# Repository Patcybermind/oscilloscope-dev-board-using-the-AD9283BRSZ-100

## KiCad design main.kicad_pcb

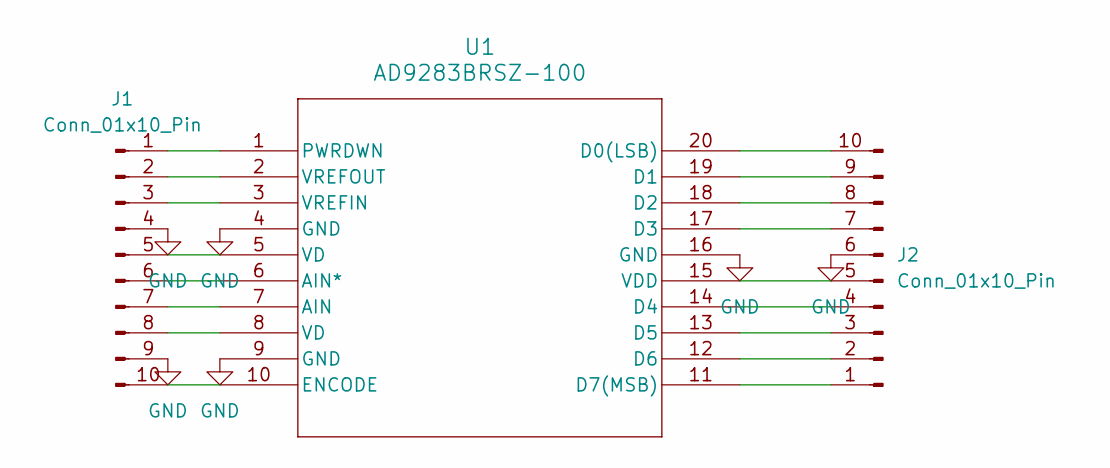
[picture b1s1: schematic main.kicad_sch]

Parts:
J1, J2: Conn_01x10_Pin; PinHeader_1x10_P2.54mm_Vertical
U1: AD9283BRSZ-100; RS_20_ADI

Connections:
GND: J1.4, J1.9, J2.6, U1.4 (GND), U1.9 (GND), U1.16 (GND)
unnamed: J1.1, U1.1 (PWRDWN)
unnamed: J1.2, U1.2 (VREFOUT)
unnamed: J1.3, U1.3 (VREFIN)
unnamed: J1.5, U1.5 (VD)
unnamed: J1.6, U1.6 (AIN*)
unnamed: J1.7, U1.7 (AIN)
unnamed: J1.8, U1.8 (VD)
unnamed: J1.10, U1.10 (ENCODE)
unnamed: J2.1, U1.11 (D7(MSB))
unnamed: J2.2, U1.12 (D6)
unnamed: J2.3, U1.13 (D5)
unnamed: J2.4, U1.14 (D4)
unnamed: J2.5, U1.15 (VDD)
unnamed: J2.7, U1.17 (D3)
unnamed: J2.8, U1.18 (D2)
unnamed: J2.9, U1.19 (D1)
unnamed: J2.10, U1.20 (D0(LSB))

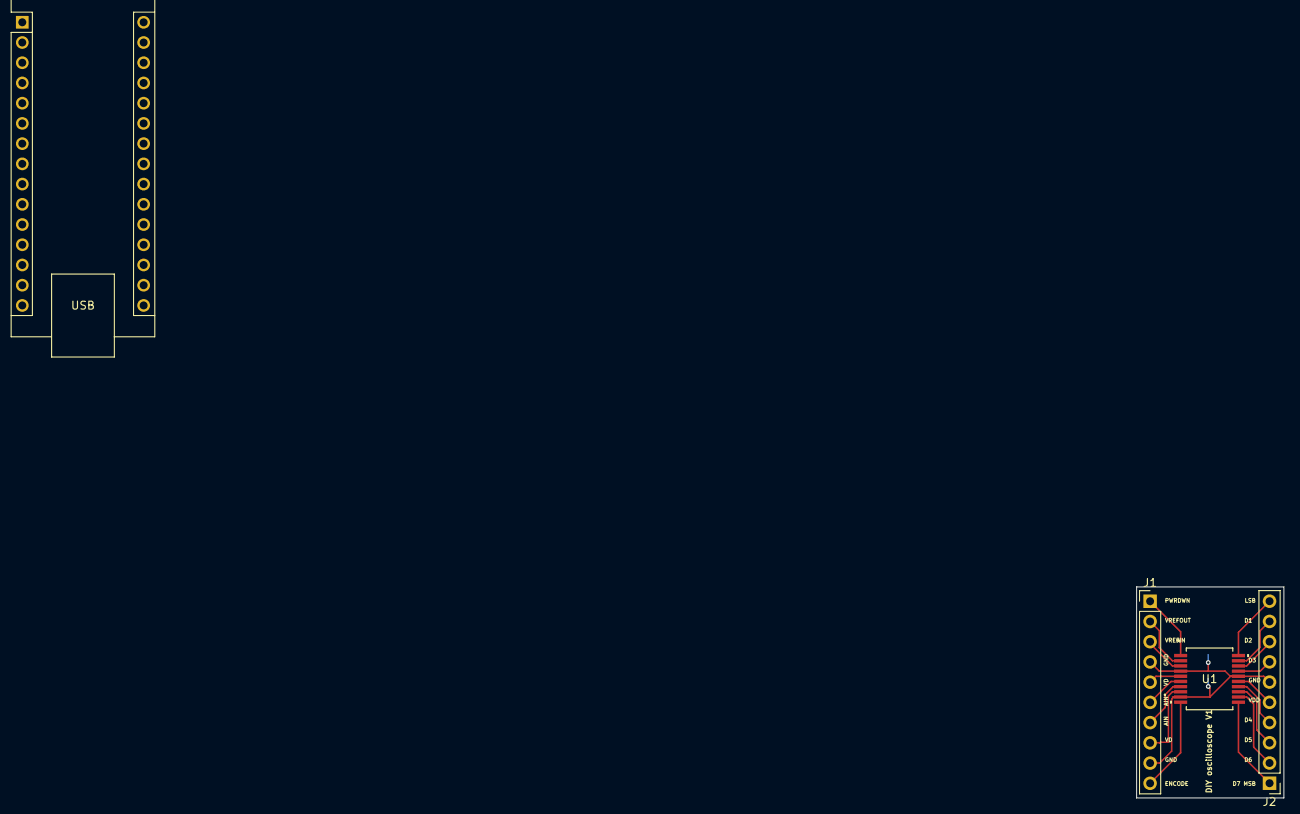
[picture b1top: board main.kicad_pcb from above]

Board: 2 copper layers, 18.5 x 26.5 mm, 4 parts (0 on the bottom side), 18 nets.

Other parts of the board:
A1: Arduino_Nano_v2.x; Arduino_Nano

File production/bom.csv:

Designator,Footprint,Quantity,Value,LCSC Part #
"J1, J2",PinHeader_1x10_P2.54mm_Vertical,2,Conn_01x10_Pin,
U1,RS_20_ADI,1,AD9283BRSZ-100,

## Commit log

2024-10-14 dev board complete
